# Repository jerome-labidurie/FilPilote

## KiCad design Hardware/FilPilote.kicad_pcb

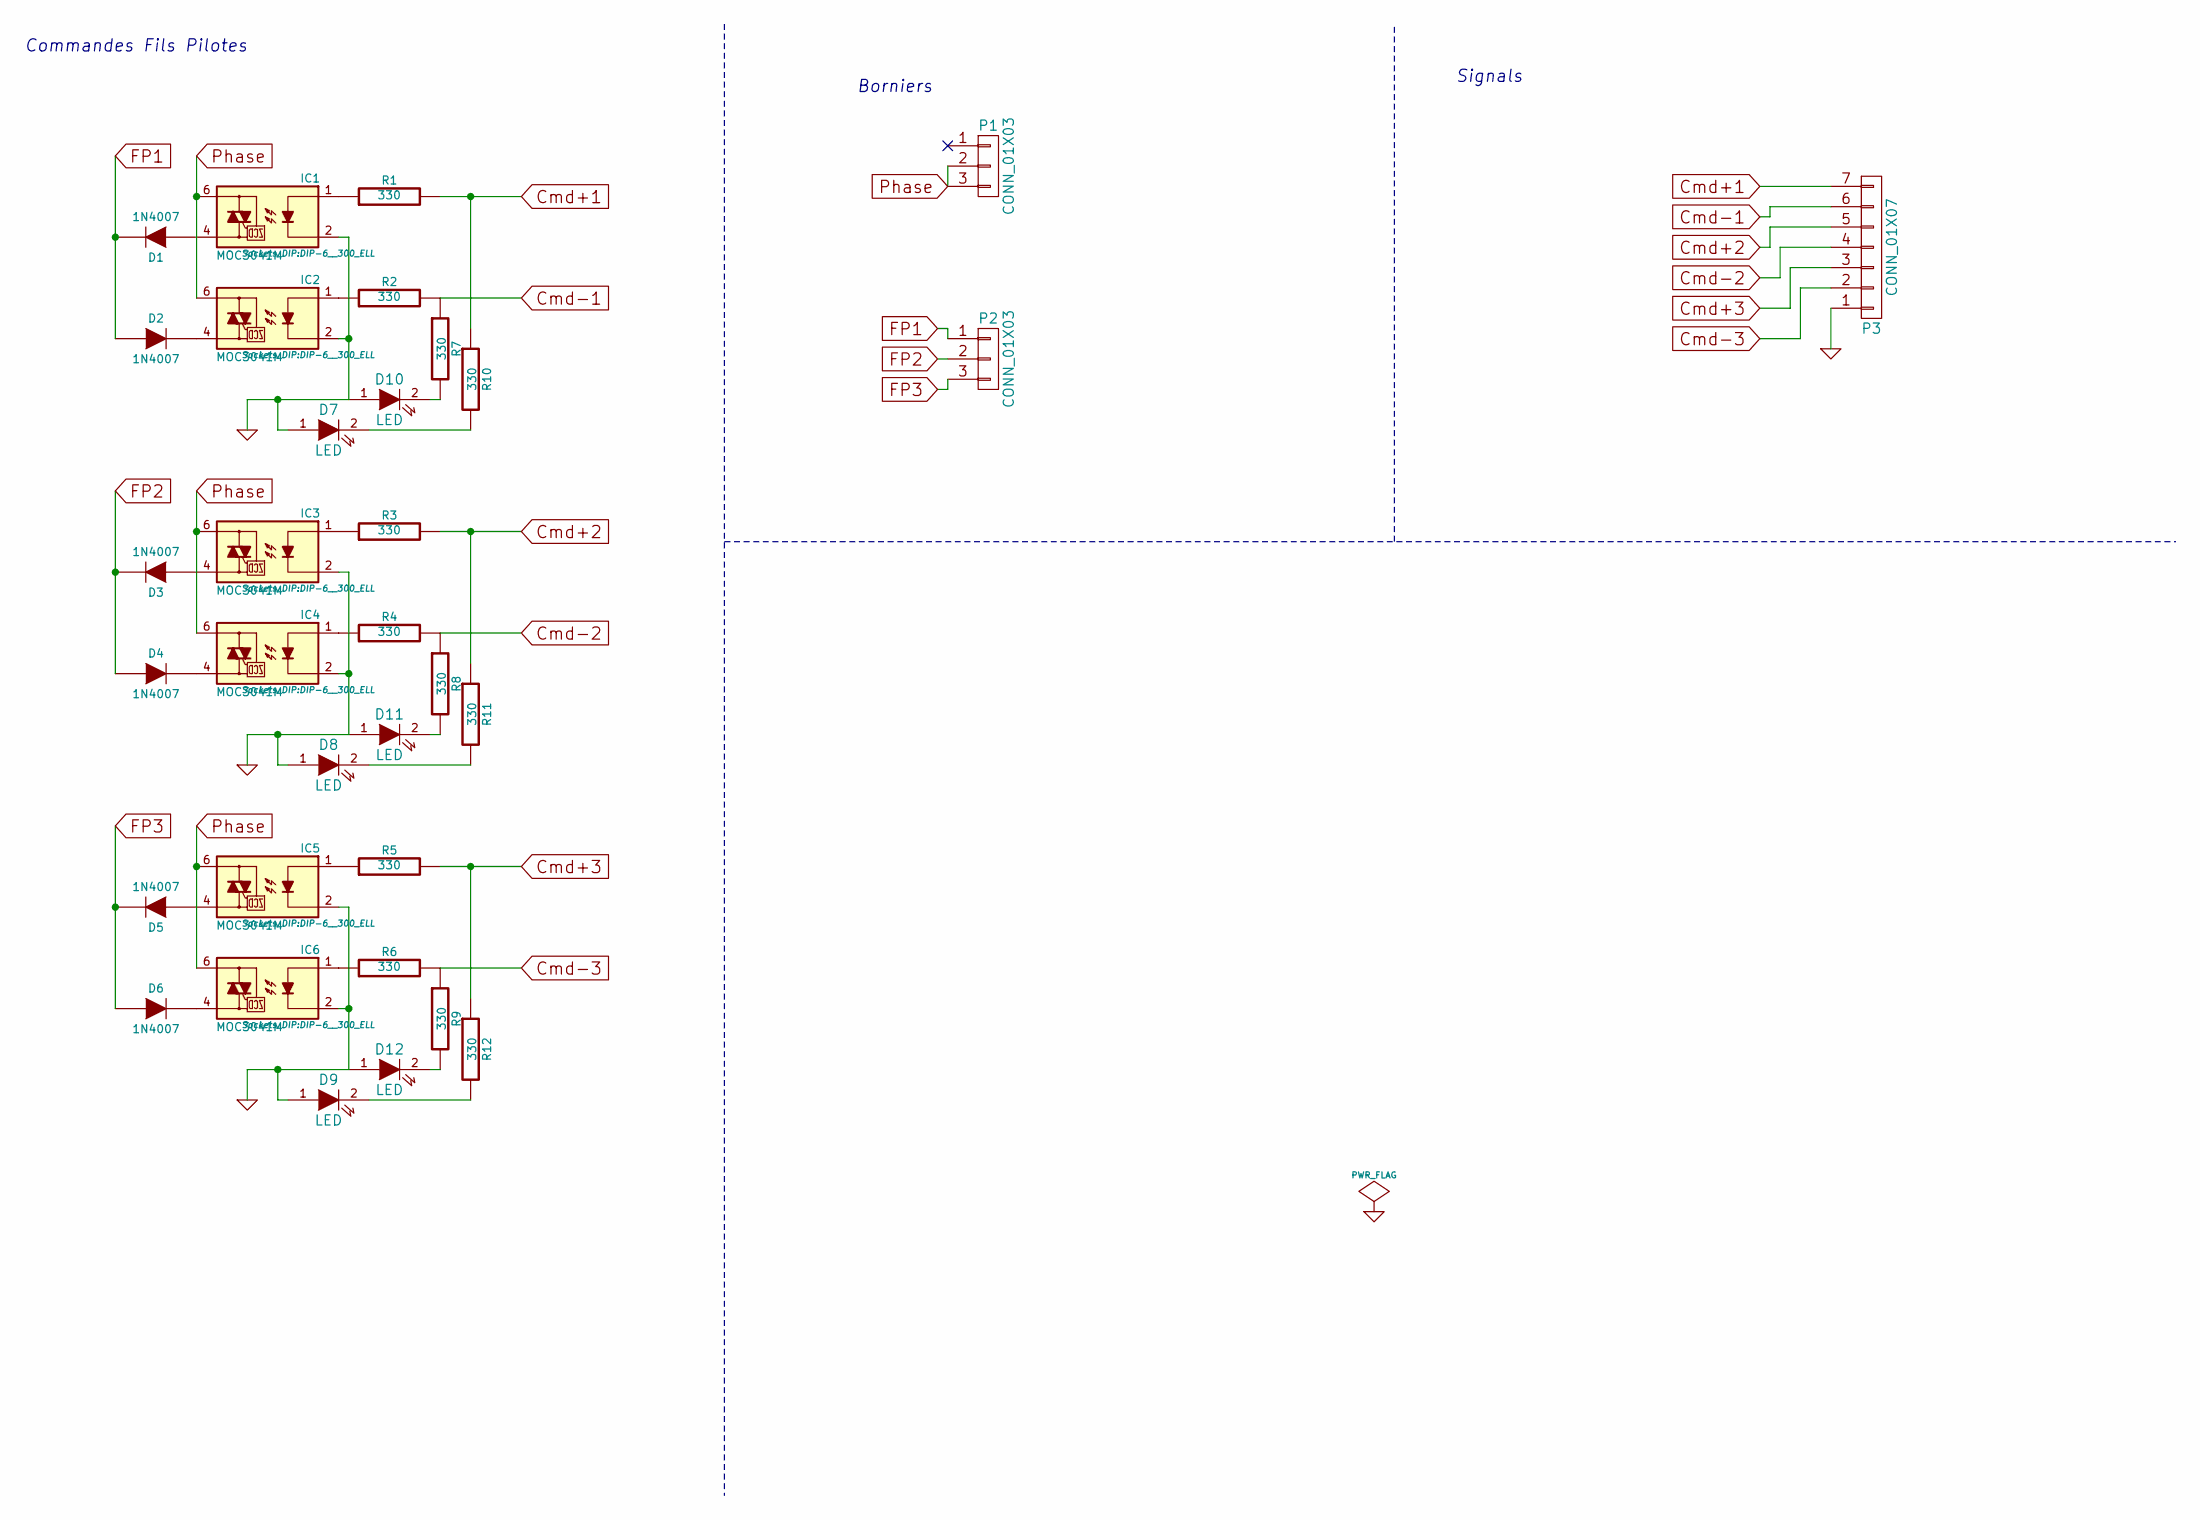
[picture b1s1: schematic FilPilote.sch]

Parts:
D1, D2, D3, D4, D5, D6: 1N4007; D4
D7, D8, D9, D10, D11, D12: LED; LED-3MM
IC1, IC2, IC3, IC4, IC5, IC6: MOC3041M; DIP-6__300_ELL
P1, P2: CONN_01X03; bornier3
P3: CONN_01X07; Pin_Header_Straight_1x07
R1, R2, R3, R4, R5, R6, R7, R8, R9, R10, R11, R12: 330; Resistor_Horizontal_RM10mm

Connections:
Cmd+1: P3.7, R1.2, R10.1
Cmd+2: P3.5, R3.2, R11.1
Cmd+3: P3.3, R5.2, R12.1
Cmd-1: P3.6, R2.2, R7.1
Cmd-2: P3.4, R4.2, R8.1
Cmd-3: P3.2, R6.2, R9.1
FP1: D1.2 (K), D2.1 (A), P2.1
FP2: D3.2 (K), D4.1 (A), P2.2
FP3: D5.2 (K), D6.1 (A), P2.3
GND: D7.1 (A), D8.1 (A), D9.1 (A), D10.1 (A), D11.1 (A), D12.1 (A), IC1.2, IC2.2, IC3.2, IC4.2, IC5.2, IC6.2, P3.1
unnamed: D1.1 (A), IC1.4
unnamed: D2.2 (K), IC2.4
unnamed: D3.1 (A), IC3.4
unnamed: D4.2 (K), IC4.4
unnamed: D5.1 (A), IC5.4
unnamed: D6.2 (K), IC6.4
unnamed: D7.2 (K), R10.2
unnamed: D8.2 (K), R11.2
unnamed: D9.2 (K), R12.2
unnamed: D10.2 (K), R7.2
unnamed: D11.2 (K), R8.2
unnamed: D12.2 (K), R9.2
unnamed: IC1.1, R1.1
unnamed: IC2.1, R2.1
unnamed: IC3.1, R3.1
unnamed: IC4.1, R4.1
unnamed: IC5.1, R5.1
unnamed: IC6.1, R6.1
Phase: IC1.6, IC2.6, IC3.6, IC4.6, IC5.6, IC6.6, P1.2, P1.3

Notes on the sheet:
Commandes Fils Pilotes
Borniers
Signals

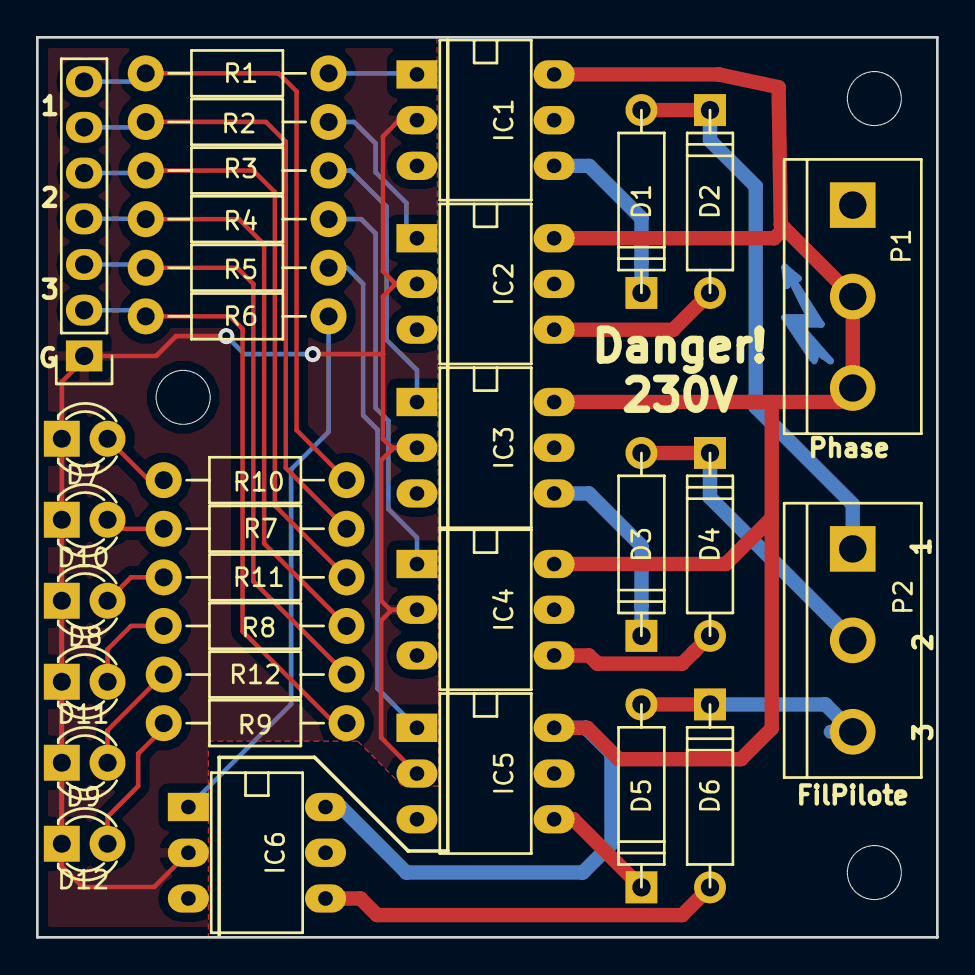
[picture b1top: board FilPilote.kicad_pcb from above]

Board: 2 copper layers, 50.0 x 50.0 mm, 33 parts (0 on the bottom side), 29 nets.

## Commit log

2015-09-20 Initial import doc hardware scheme
2015-09-22 Remove useless earth connection
2015-09-22 Label "Danger!"
2015-09-25 Add architecture drawing
2015-09-25 Complete architecture
2015-09-27 Move to kicad 4.0.0 RC1
2015-10-10 Add fabrication files
2015-10-19 Add drill file
2015-11-21 Add real cabling to architecture
2015-11-21 Add arduino software
2015-11-22 Add bash script bugfix #ifdef mode Eco
2016-11-13 Add lowercase commands
2017-02-06 Blink
2020-09-15 Add python version
2020-09-15 Add timeout
